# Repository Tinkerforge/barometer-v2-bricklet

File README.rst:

Barometer Bricklet 2.0
======================

This repository contains the firmware source code and the hardware design
files. The documentation generator configs can be found at
https://github.com/Tinkerforge/generators

Repository Content
------------------

software/:
 * examples/: Examples for all supported languages
 * build/: Compiled files
 * src/: Source code of firmware
 * Makefile: Makefile to build project

hardware/:
 * Contains KiCad project files and additionally schematics as PDF

datasheets/:
 * Contains datasheets for sensors and complex ICs that are used

Hardware
--------

The hardware is designed with the open source EDA Suite KiCad
(http://www.kicad.org). Before you are able to open the files,
you have to install the Tinkerforge kicad-libraries
(https://github.com/Tinkerforge/kicad-libraries). You can either clone
them directly in hardware/ or clone them in a separate folder and
symlink them into hardware/
(ln -s kicad_path/kicad-libraries project_path/hardware). After that you
can open the .pro file in hardware/ with KiCad and from there view and
modify the schematics and the PCB layout.

Software
--------

If you want to do your own Brick/Bricklet firmware development we highly
recommend that you use our build environment setup script and read the
tutorial (https://www.tinkerforge.com/en/doc/Tutorials/Tutorial_Build_Environment/Tutorial.html).

To compile the C code we recommend you to install the newest GNU Arm Embedded
Toolchain (https://launchpad.net/gcc-arm-embedded/+download).
You also need to install bricklib2 (https://github.com/Tinkerforge/bricklib2).

You can either clone it directly in software/src/ or clone it in a
separate folder and symlink it into software/src/
(ln -s bricklib_path/bricklib2 project_path/software/src/). Finally make sure to
have CMake installed (http://www.cmake.org/cmake/resources/software.html).

After that you can build the firmware by invoking make in software/.
The firmware (.zbin) can then be found in software/build/ and uploaded
with brickv (click button "Flashing" on start screen).

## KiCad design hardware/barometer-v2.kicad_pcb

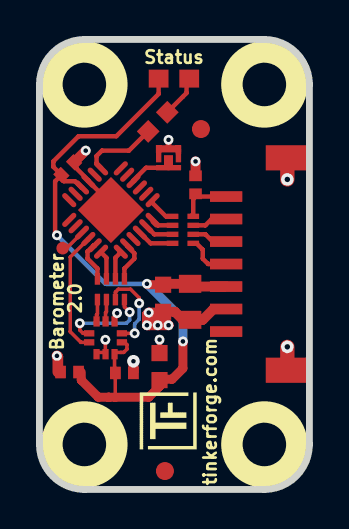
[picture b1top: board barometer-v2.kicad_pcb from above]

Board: 2 copper layers, 15.0 x 25.0 mm, 24 parts (0 on the bottom side), 23 nets.

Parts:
C1: 220pF; C0402F
C2: 10uF; C0805
C3, C7: 1uF; C0603F
C4: 100n; C0402F
C5, C6: 100nF; C0402F
D1: blue; D0603E
Fiducial_Mark: VAL**; Fiducial_Mark
Fiducial_Mark#2: VAL**; Fiducial_Mark
P1: CON-SENSOR2
P2: CONN_01X01; DEBUG_PAD
P3: BOOT; SolderJumper
R1: 1k; R0603F
RP1, RP2: 82; 4X0402
U1: XMC11XX24; QFN24-4x4mm-0.5mm
U2: LPS22HB; HLGA-10L
U3, U4, U5, U6: DRILL; DRILL_NP
VAL: CE_5mm
VAL#2: WEEE_7mm

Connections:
GND: C1.2, C2.2, C3.2, C4.1, C5.1, C6.2, C7.1, P1.2, P1.EP, P3.1, U1.9, U1.EXP, U2.3, U2.8, U2.9
INT: U1.16, U2.7
M-CLK: RP2.3, U2.2
M-CS: RP2.4, U2.6
M-MISO: RP2.1, U2.5
M-MOSI: RP2.2, U2.4
unnamed: C1.1, P1.7, RP1.4
unnamed: D1.2, R1.2
unnamed: P1.4, RP1.1
unnamed: P1.5, RP1.2
unnamed: P1.6, RP1.3
unnamed: P2.1, U1.15
unnamed: P3.2, U1.4
unnamed: R1.1, U1.7
unnamed: RP2.5, U1.20
unnamed: RP2.6, U1.19
unnamed: RP2.7, U1.18
unnamed: RP2.8, U1.17
S-CLK: RP1.7, U1.23
S-CS: RP1.8, U1.22
S-MISO: RP1.5, U1.1
S-MOSI: RP1.6, U1.24
VCC: C2.1, C3.1, C4.2, C5.2, C6.1, C7.2, D1.1, P1.3, U1.10, U2.1, U2.10

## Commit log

2017-08-30 Add datasheets
2017-08-30 Add schematic
2017-08-30 Add capacitor
2017-08-30 Fix footprints
2017-08-30 Add unfinished version of PCB
2017-09-13 Add early version of PCB
2017-09-13 Place CE logo
2017-09-14 Place fiducials and WEEE logo
2017-09-14 Change RP2, add CoMCU logo
2017-09-14 Add missing GND via
2017-09-27 fix footprint, routing not completed
2017-10-13 Fix routing
2017-11-15 change 0402E footprints to 0402F
2017-12-04 Add 3d information (prefinal)
2018-02-20 Add .gitignore
2018-02-20 Cleanup KiCad libraries config
    Ensure LibDir=kicad-libraries and LibName1=tinkerforge.
    Remove special library.
2018-04-16 Initial firmware commit
2018-04-17 fix sensor footprint
2018-05-07 Rename datasheet
2018-05-11 Rename files
2018-05-16 Firmware implementation
2018-05-16 Add technical note
2018-05-17 barometer-v2: Air pressure handled as mbar/1000, reference air pressure type changed to int32_t, calibration parameters are measured and reference air pressure
2018-05-17 Check CTRL_REG2 for new data ready bit
2018-06-06 fix logo positions
2018-06-06 fix status text
2018-06-06 Adapt to bricklib2 callback-value changes to fix wrong threshold min/max type
2018-06-28 Fix readme
2018-07-11 Add Makefile with docker support
2018-07-11 Remove obsolete generate_makefile scripts
2018-07-11 Update directory structure and build instructions
2018-07-17 specify processor
2018-07-31 Add 3d model (*.FCStd & *.step)
2018-07-31 Add PDF schematic
2018-09-10 Add examples
    LabVIEW examples missing.
2018-09-11 Fix invalid parameter checks
2018-09-11 Move calibration logic to tick
2018-09-14 Replace SPI FIFO flushing with proper reading
2018-09-14 vbnet: Fix typo in comment
2018-09-19 Rework entire sensor reading logic
    Switch from state-machine to co-op task.
    Use configurable data-rate with interrupt pin instead of one-shot loop.
    Make data-rate and low-pass-filter user-configurable.
    Remove unnecessary altitude moving average to free some RAM for the
    co-op task handling.
2018-09-21 Add LabVIEW examples
2018-10-02 Add BOOTLOADER_FIX_POINTER_END define
2018-10-04 Add rev to changelog
2018-10-16 Remove in-development marker
2018-11-06 Add rust examples
2018-11-07 rust: Accept host names for ip connection, fix naming inconsistencies
2018-11-07 rust: Rename callback receivers.
2018-12-14 Add go examples.
2018-12-14 go: Fix printf parameters.
2018-12-18 go: Change import path.
2018-12-18 go: Change import path again.
2018-12-20 rust: Reformat examples.
2019-01-24 mqtt: Add examples.
2019-01-24 mqtt: Fix example header.
2019-01-24 mqtt: Remove executable bit in example permissions.
2019-01-24 go: Minor example fixes.
2019-01-24 mqtt: Minor example fixes.
2019-03-28 mqtt: Fix whitespace.
2019-05-29 Activate memory optimized irq handler
    The Barometer Bricklet 2.0 has very little flash left. Since
    it does not use any IRQs itself, it can use the memory optimized
    version of the new bootloader SPI IRQ implementation without any
    drawbacks. Otherwise we would run out of flash here.
2019-06-03 Fix typo in define
2019-08-22 c: Adapt to bindings changes
2019-11-22 Update examples
2020-01-13 examples: Use python3 input instead of python2 raw_input.
2020-01-13 examples: mqtt: Remove trailing whitespace.
2020-08-19 Add uc examples.
2020-08-25 uc: Fix whitespace
2020-08-27 uc: Fix warnings.
2020-09-02 uc: Add example driver note.
2020-10-16 uc: Fix divisor type.
2021-10-25 Update KiCad link
    https://www.kicad.org/blog/2021/10/Avoid-links-to-former-kicad-domain/
2022-04-19 examples: uc: Rename TF_HalContext to TF_HAL.
2022-04-27 uc: Adapt to bindings changes
2022-07-06 Add license files.
2023-03-09 labview: Fix callback example
    Seems to be callback data type issue.
2025-10-04 Fix compatibility with new Docker build image (GCC 14.2.1)

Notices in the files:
hardware/barometer-v2.kicad_pcb:
Licensed under CERN OHL v.1.1
Copyright (©) 2017, L.Lauer
Copyright Tinkerforge GmbH 2017.
This documentation describes Open Hardware and is licensed under the
CERN OHL v. 1.1.
